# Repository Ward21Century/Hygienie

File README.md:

# Hygienie Project

This is the refactored code for hygienie-2022 refactored project that uses the esp-idf framework. This means that source code has been refactored into modules, unit-tests have been written for each module and can be run on the esp32 itself for regression testing, and that project values such as wifi network, password, device id, and sleep duration can be entered in a terminal menu.

## Project layout

```
hygienie_project                      — Application project directory
  - components                 — Components of the application project
    + appdata                  — Module that describes how the data is structured.
    + appgraphics              — Module that uses graphics libary and displays animations
    + appmqtt                  — Module that encapsulates mqtt client
    + appsleep                 — Module that controls esp32 sleep  mode
    + appwifi                  — Module that encapsulates wifi libraries
  + main                       - Main source files of the application project
  - test                       — Test project directory
    - main                       — test main directory for test runner
      + hygienie_unit_test.c   — hygienie test runner.
  Makefile / CMakeLists.txt    - Makefiles of the application project
```

The two projects, main, and test/main, can implement different application behavior when running normally, and when running the unit tests. Top level project is the actual application being developed. Test project included within is a simple application which only runs the unit tests.

## Unit tests for a component

Inside the `testable` component, unit tests are added into `test` directory. `test` directory contains source files of the tests and the component makefile (component.mk / CMakeLists.txt).

```
unit_test
  - components                              - Components of the application project
    - testable
      - include
      - test                                - Test directory of the component
        * component.mk / CMakeLists.txt     - Component makefile of tests
        * test_mean.c                       - Test source file
      * component.mk / CMakeLists.txt       - Component makefile
      * mean.c                              - Component source file
```

When the main application project is compiled, tests are not included. Test project includes the tests by setting `TEST_COMPONENTS` variable in the project makefile.

## Requirements

### Hardware required

* FireBeetle DFR0478, but any esp32 board will work.
* USB cable - USBA/

### Software Requirements
Please look at https://docs.espressif.com/projects/esp-idf/en/latest/esp32/get-started/
for installing esp-idf and https://docs.espressif.com/projects/esp-idf/en/latest/esp32/get-started/linux-macos-setup.html#get-started-linux-macos-first-steps
for configuring and building project on command line.

It is recommended that you run:
```
. $HOME/esp/esp-idf/export.sh
```
in your terminal.

and create the alias:
```
alias get_idf='. $HOME/esp/esp-idf/export.sh'# Configure the project
```
For the menu_config:

For the test project, you can open the project configuration menu (`idf.py menuconfig`) and explore a few options related to Unity under Component Config, Unity unit testing library.

### Build and flash

As explained above, this example contains two projects: application project and test project.

1. Application project calls an API defined in the component, and displays the results. It is not of much value to run. Application project is provided mainly to illustrate the layout of all the files. If you decide to run this project, the procedure is:

    * Run `idf.py -p PORT flash monitor` in the current directory (`unit_test`).
    * Observe the output: a list of random numbers and their mean value.

2. Test project is responsible for running the tests.

	* Enter `test` directory (`unit_test/test`), and run `idf.py -p PORT flash monitor`.
	* Observe the output: results of test case execution.

See the Getting Started Guide for full steps to configure and use ESP-IDF to build projects.

## Unit Testing

Inside the `testable` component, unit tests are added into `test` directory. `test` directory contains source files of the tests and the component makefile (component.mk / CMakeLists.txt).

```
unit_test
  - components                              - Components of the application project
    - testable
      - include
      - test                                - Test directory of the component
        * component.mk / CMakeLists.txt     - Component makefile of tests
        * test_mean.c                       - Test source file
      * component.mk / CMakeLists.txt       - Component makefile
      * mean.c                              - Component source file
```

When the main application project is compiled, tests are not included. Test project includes the tests by setting `TEST_COMPONENTS` variable in the project makefile.
### Application project output

```
In main application. Collecting 32 random numbers from 1 to 100:
   5   66   86   98   62   66   40   42    7   62
  33   77   40   54    8   75   39   82   73    4
  22    5   72   78   53    1    6   48   23    1
  84   55
Mean: 45
```

### Test project output

```
#### Executing one test by its name #####

Running Mean of an empty array is zero...
/Users/ivan/e/esp-idf/examples/system/unit_test/components/testable/test/test_mean.c:16:Mean of an empty array is zero:PASS

-----------------------
1 Tests 0 Failures 0 Ignored
OK

Running Mean of an empty array is zero...
/home/user/esp/esp-idf/examples/system/unit_test/components/testable/test/test_mean.c:15:Mean of an empty array is zero:PASS
Test ran in 16ms

-----------------------
1 Tests 0 Failures 0 Ignored
OK
Enter next test, or 'enter' to see menu
```

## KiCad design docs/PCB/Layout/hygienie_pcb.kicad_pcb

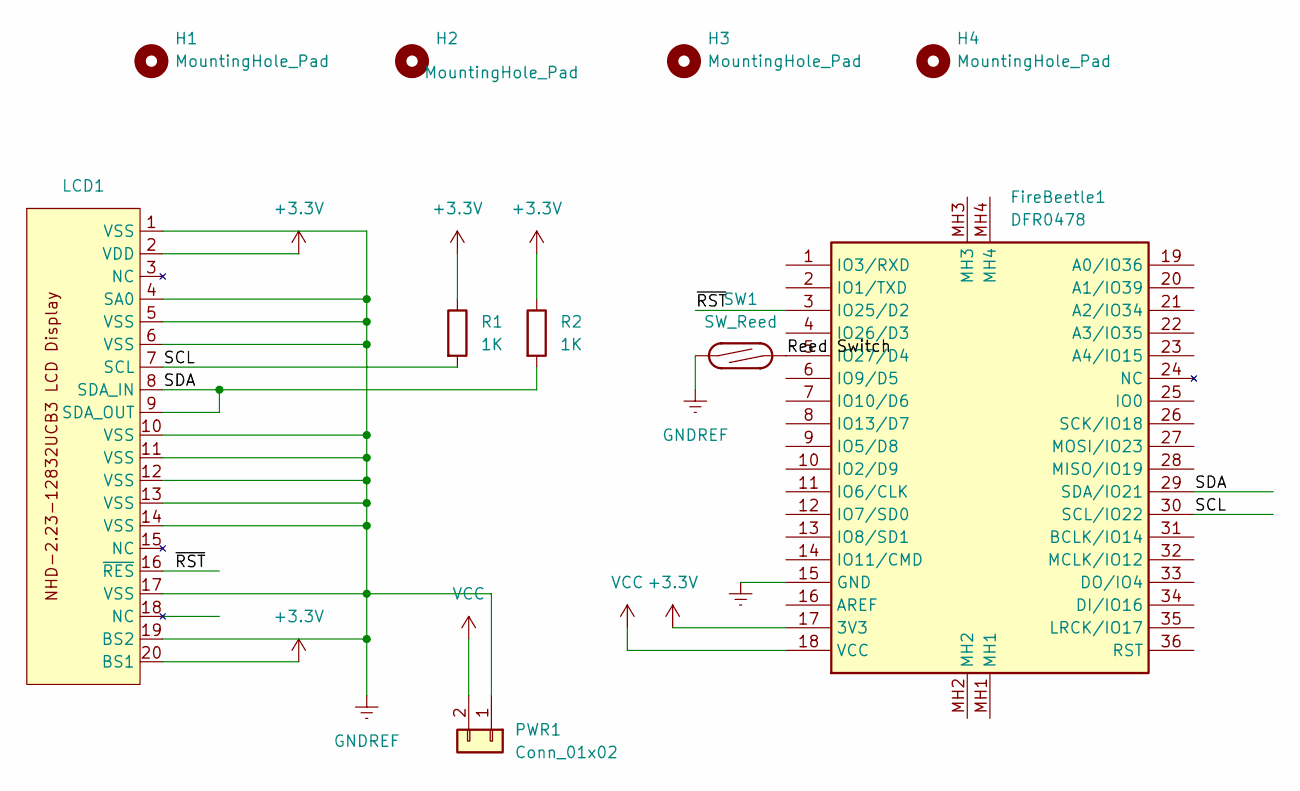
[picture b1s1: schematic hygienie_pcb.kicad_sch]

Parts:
FireBeetle1: DFR0478; FIREBEETLE_ESP32_Hygienie_Mod; Manufacturer_Part_Number DFR0478
H1, H2, H3, H4: MountingHole_Pad; MountingHole_2.5mm
LCD1: PinHeader_1x20_P2.54mm_Vertical
PWR1: Conn_01x02; PinHeader_1x02_P2.54mm_Vertical
R1, R2: 1K; R_0603_1608Metric
SW1: SW_Reed; R_Axial_DIN0614_L14.3mm_D5.7mm_P15.24mm_Horizontal

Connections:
+3.3V: FireBeetle1.17 (3V3), LCD1.2 (VDD), LCD1.20 (BS1), R1.1, R2.1
/Reed Switch: FireBeetle1.5 (IO27/D4), SW1.2
/SCL: FireBeetle1.30 (SCL/IO22), LCD1.7 (SCL), R1.2
/SDA: FireBeetle1.29 (SDA/IO21), LCD1.8 (SDA_IN), LCD1.9 (SDA_OUT), R2.2
/~RST: FireBeetle1.3 (IO25/D2), LCD1.16 (~RES)
GNDREF: FireBeetle1.15 (GND), LCD1.1 (VSS), LCD1.4 (SA0), LCD1.5 (VSS), LCD1.6 (VSS), LCD1.10 (VSS), LCD1.11 (VSS), LCD1.12 (VSS), LCD1.13 (VSS), LCD1.14 (VSS), LCD1.17 (VSS), LCD1.19 (BS2), PWR1.1, SW1.1
VCC: FireBeetle1.18 (VCC), PWR1.2

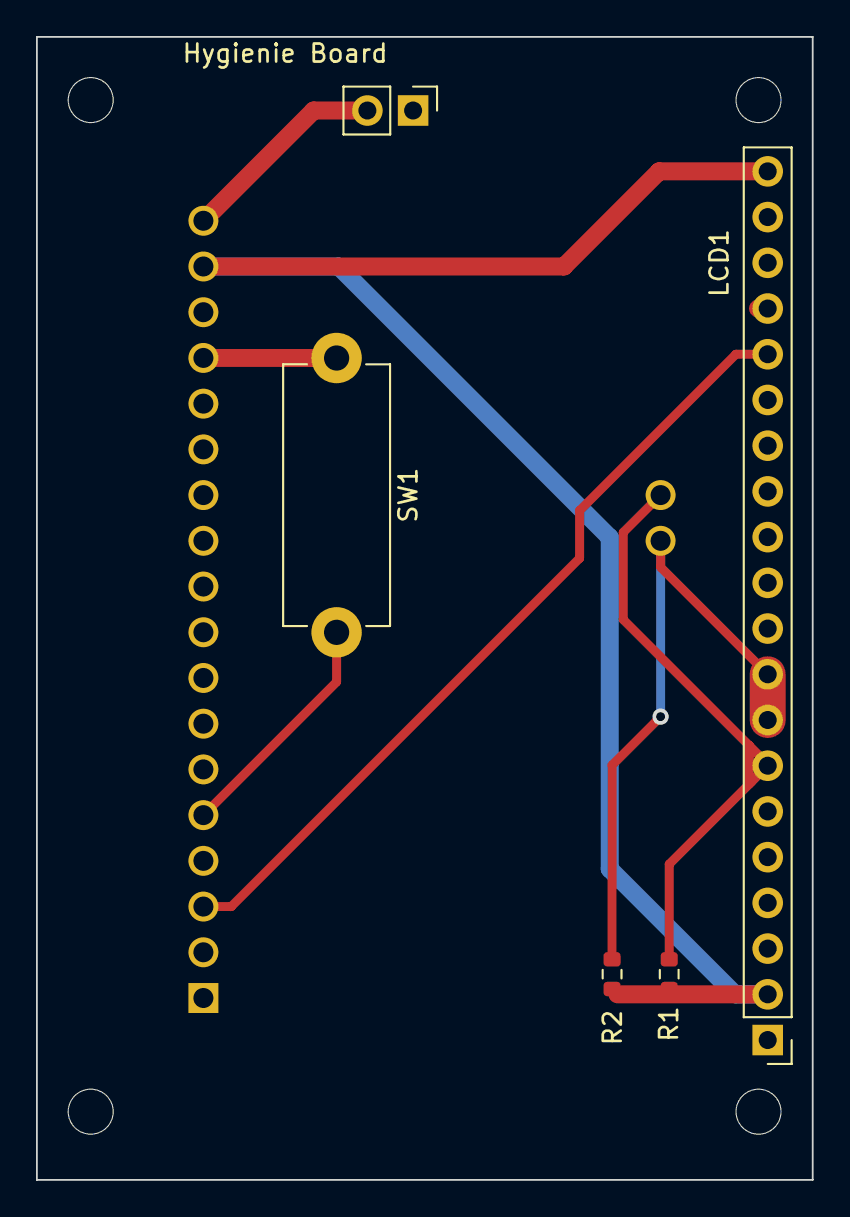
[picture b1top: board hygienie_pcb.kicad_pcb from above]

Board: 2 copper layers, 43.1 x 63.5 mm, 10 parts (1 on the bottom side), 7 nets.

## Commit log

2022-11-15 Made changes to the main function.
2022-11-15 Added u8g2_hal_esp_idf into repository.
2022-11-15 u8g2 was removed.
2022-11-15 Added u8g2 submodule component.
2023-02-15 Added new libaries for unit testing.
2023-02-19 Added AppGraphics as a separate module with test cases.
2023-02-19 Renamed 'Appgraphics' module to 'appgraphics' module
2023-02-20 Added AppSleep. This allows the app to sleep by a touchpad and a timer.
2023-02-27 Added components required for appmqtt and restructed component directories by placing header files in include directory.
2023-02-27 Modified root CMakeLists so that it includes commong protocol component. Also changed appdata and appmqtt.
2023-03-06 Added simple wifi module that creates a station, and modified struct that uses time info.
2023-03-06 Added a delay between animations just like what arduino has.
2023-05-24 Added test cases to appgraphics and additional driver to appgraphics.
2023-05-27 Added ntp synchronization in addition to configuring application server via Kconfig.
2023-05-27 Max Num of Offline Recording can now be configured in menuconfig.
2023-05-30 Fiddled with pdMS_TO_TICKS so connection for mqtt doesn't time out.
2023-05-30 Adding a git ignore.
2023-05-30 Removed build folders from remote repo.
2023-05-30 Removed unecessary build folders and logs.
2023-05-30 Removed tags.
2023-05-30 Removing more extraneous files.
2023-08-07 Debuggin files.
2023-08-14 Cleaning up some code and removing extraneous commits.
2023-08-14 Renamed 'example_unit_test_test.c' to 'hygienie_unit_test.c'
2023-08-14 Edited the README.md
2023-08-14 Further edited README.md
2023-08-14 Added a docs file for documentation.
2023-08-14 Further edited README.md files.
2023-08-14 Cleaning up commented out code.
2023-08-23 Modified driver for new display.
2023-08-23 Debugged ssd_1305_driver.
2023-08-29 Removed hard coded value for wake up threshold that was used for debugging.
2023-09-03 Changed variables types that were previously integer to uint32_t.
2023-09-03 Adding Removed extraneous macros and placing defines from AppGraphics.c to Appgraphics.h
2023-09-24 Added PCB schematic, gerber files, and screenshots of both schematic and PCB layout.
2023-11-22 Fixed bug where grpahics was still displayed incorrectly.
2023-11-22 Changed logging for appsleep.c
2024-03-11 Added some user-configurable values at run-time, such as mqtt_uri and device id.
2024-03-11 Appmqtt uses user-configurable values as well.
2024-03-11 New functions were added in AppSleep due to refacotring, such as getting_wake_up_cause and returning it to app_main
2024-03-11 Reorganized flow of code in main.c for better readability.
2024-03-24 Create separate functions for initializing ntp server.
2024-03-25 Fixed timestamp issue. Cleaned up unused variables.
2024-04-05 Forked u8g2-hal-esp-idf to alter i2c_clk_speed to 100000 Hz and altered .gitmodules so it's faster.
2024-04-05 Changed file names appmqtt and appdata so that it conforms with camel case style.
2024-04-05 Adding renamed files to git repository.
2024-05-30 Raised minimum threshold for touchpad to wake up to prevent false postives.
2024-06-10 Rewrote AppSleep so that GPIO takes an interrupt rather than apptouch.
2024-08-05 Created new pin that enables LCD converter. Also configured gpio pins for normal opearation and for deep sleep to minimize power consumption
2024-08-25 WIP: Still in debugging mode. Changed touch_pad pin to an external wake up pin to conserve more power.
2024-08-25 Removing all debugging code from main.c
2024-11-30 Altered gpio_initialization for AppGraphics.c. It turns out initializing the GPIO that controls LCD converter with a pull down removes the hard fault
2024-11-30 Removed logging from AppSleep.c
2024-11-30 Changed 'AppSleepTouchWakeUpInit' to 'AppSleepWakeUpInit'
2024-12-14 Removed extraneous Kconfig configurations and removed associated definitions in AppSleepConfig.h
2024-12-15 Changed branch to look in for submodule
2024-12-15 Changed .gitmodule so submoodule isn't tracked to differen repo
2024-12-15 Change to new commit on different branch
2025-08-24 Added include guards to header files
2025-08-25 Added include guards for appwifi.h and cleaned up code for main.c so it's more readable
2025-08-25 Added some debug logs to make sure GPIO for REED SWITCH is pulled up
2025-08-25 Renamed pin 27 to ites respective macro
